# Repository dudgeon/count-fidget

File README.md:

# Count Fidget

A lightweight, rechargeable two-key fidget that counts clicks, resets with a second key, and remembers its count while asleep or unpowered. Designed for a home-printed enclosure and professionally assembled electronics.

**Q5 is the active engineering candidate:** the Q4 STM32L072CBT6 / USB-C home programming / SPI OLED / SPI FRAM design, plus:
- a soft power key (COUNT turns it on; it switches itself off after 30 s, drawing ~8 µA);
- a vendor-soldered LIR2032 coin-cell holder in place of a custom battery pack;
- a battery gauge with LO warning and storage cut-off, and charge status;
- a reset pinhole;
- hold-to-reset key logic;
- a smaller 47.2 × 59.2 × 16.8 mm printed enclosure with printed keycaps;
- solder-free keys (clicky switches pressed into vendor-placed hot-swap sockets).

JLC performs all SMT from standard inventory parts. Two JLCPCB variants are prepared:
- **A:** the user solders the display header (14 joints);
- **B:** JLC also fits the display.

Q1–Q4 remain historical, unchanged packages.

**The design is locked, and a first-article batch of 5 assembled boards was ordered from JLCPCB on 26 September 2026** (see [JLC-QUOTE-Q5](procurement/q5/JLC-QUOTE-Q5.md)). Nothing has been built or measured yet. The boards will be checked against the [first-article test plan](docs/q5-first-article-test-plan.md).

Start with [the Q5 engineering review](docs/REVIEW-Q5-2026-09-25.md), [PROJECT.md](PROJECT.md) for status, and [HANDOFF.md](HANDOFF.md) for continuation.

| Area | Current Q5 files |
|---|---|
| PCB | [KiCad project](electronics/q5/click-counter-Q5.kicad_pro), [board](electronics/q5/click-counter-Q5.kicad_pcb), [schematic PDF](electronics/q5/schematic-Q5.pdf), [power design](docs/q5-power-design.md) |
| Firmware and programming | [Q5 source/build](firmware/q5-stm32/README.md), [keys, power and USB procedure](docs/q5-firmware.md), [macOS flashing tool](tools/clicker-flash/README.md) (Claude skill `flash-clickers`) |
| Inventory, assembly and quote | [Stock evidence](procurement/q5/stock.json), [exports](procurement/q5/REVIEW-EXPORTS-Q5.md), [JLCPCB quote and estimate](procurement/q5/JLC-QUOTE-Q5.md) |
| Enclosure | [Assembly and parts](mechanical/q5/README.md), [rendering](mechanical/q5/assembled-Q5.png), [STEP assembly](mechanical/q5/enclosure-Q5.step) |
| Verification | [Build workflow](docs/build-and-verify.md), Q5 reports in `verification/`, [firmware emulation](simulation/q5-firmware-emulation/README.md), [bounded power checks](simulation/q5-power/result.json) |
| Product history | [Specification](docs/product-spec.md), [user context](docs/user-research.md), [decisions](docs/decisions.md), [Q4 review](docs/REVIEW-Q4-2026-09-24.md), [Q4 simulation review](docs/REVIEW-Q4-simulation-2026-09-25.md) |
| Vendor history | [Vendor status](procurement/vendor-status.md); retained RFQ packages in `dist/` do not authorize new submissions |

Quick checks, with Python 3 and a C compiler:

```sh
python3 scripts/verify_project.py
python3 scripts/run_host_tests.py
```

These verify files, package consistency and portable firmware logic, not physical electronics. Toolchains, credentials, private mailbox content and customer account sessions are not stored in this public repository.

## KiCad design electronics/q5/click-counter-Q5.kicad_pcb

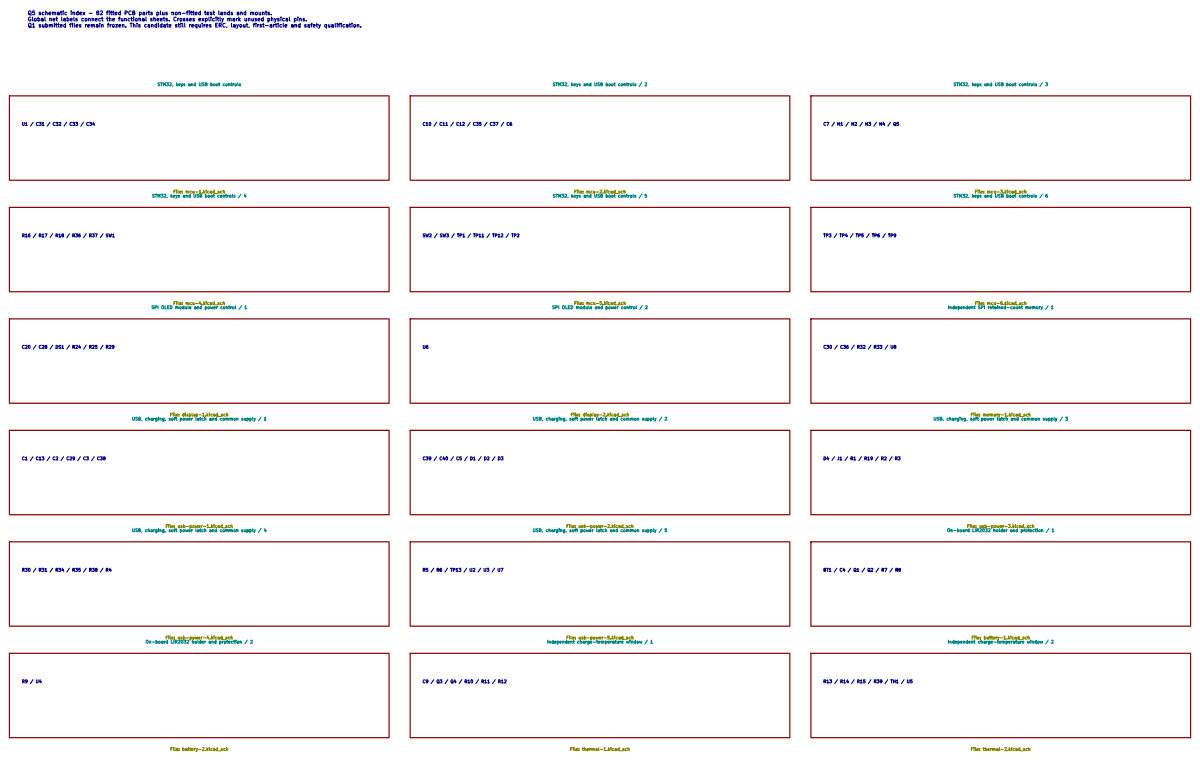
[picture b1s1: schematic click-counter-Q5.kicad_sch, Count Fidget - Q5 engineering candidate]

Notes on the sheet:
Q5 schematic index - 82 fitted PCB parts plus non-fitted test lands and mounts. Global net labels connect the functional sheets. Crosses explicitly mark unused physical pins. Q1 submitted files remain frozen. This candidate still requires ERC, layout, first-article and safety qualification.
U1 / C31 / C32 / C33 / C34
C10 / C11 / C12 / C35 / C37 / C6
C7 / H1 / H2 / H3 / H4 / Q5
R16 / R17 / R18 / R36 / R37 / SW1
SW2 / SW3 / TP1 / TP11 / TP12 / TP2
TP3 / TP4 / TP5 / TP6 / TP9
C20 / C28 / DS1 / R24 / R25 / R29
C30 / C36 / R32 / R33 / U8
C1 / C13 / C2 / C29 / C3 / C38
C39 / C40 / C5 / D1 / D2 / D3
D4 / J1 / R1 / R19 / R2 / R3
R30 / R31 / R34 / R35 / R38 / R4
R5 / R6 / TP13 / U2 / U3 / U7
BT1 / C4 / Q1 / Q2 / R7 / R8
R9 / U4
C9 / Q3 / Q4 / R10 / R11 / R12
R13 / R14 / R15 / R39 / TH1 / U5

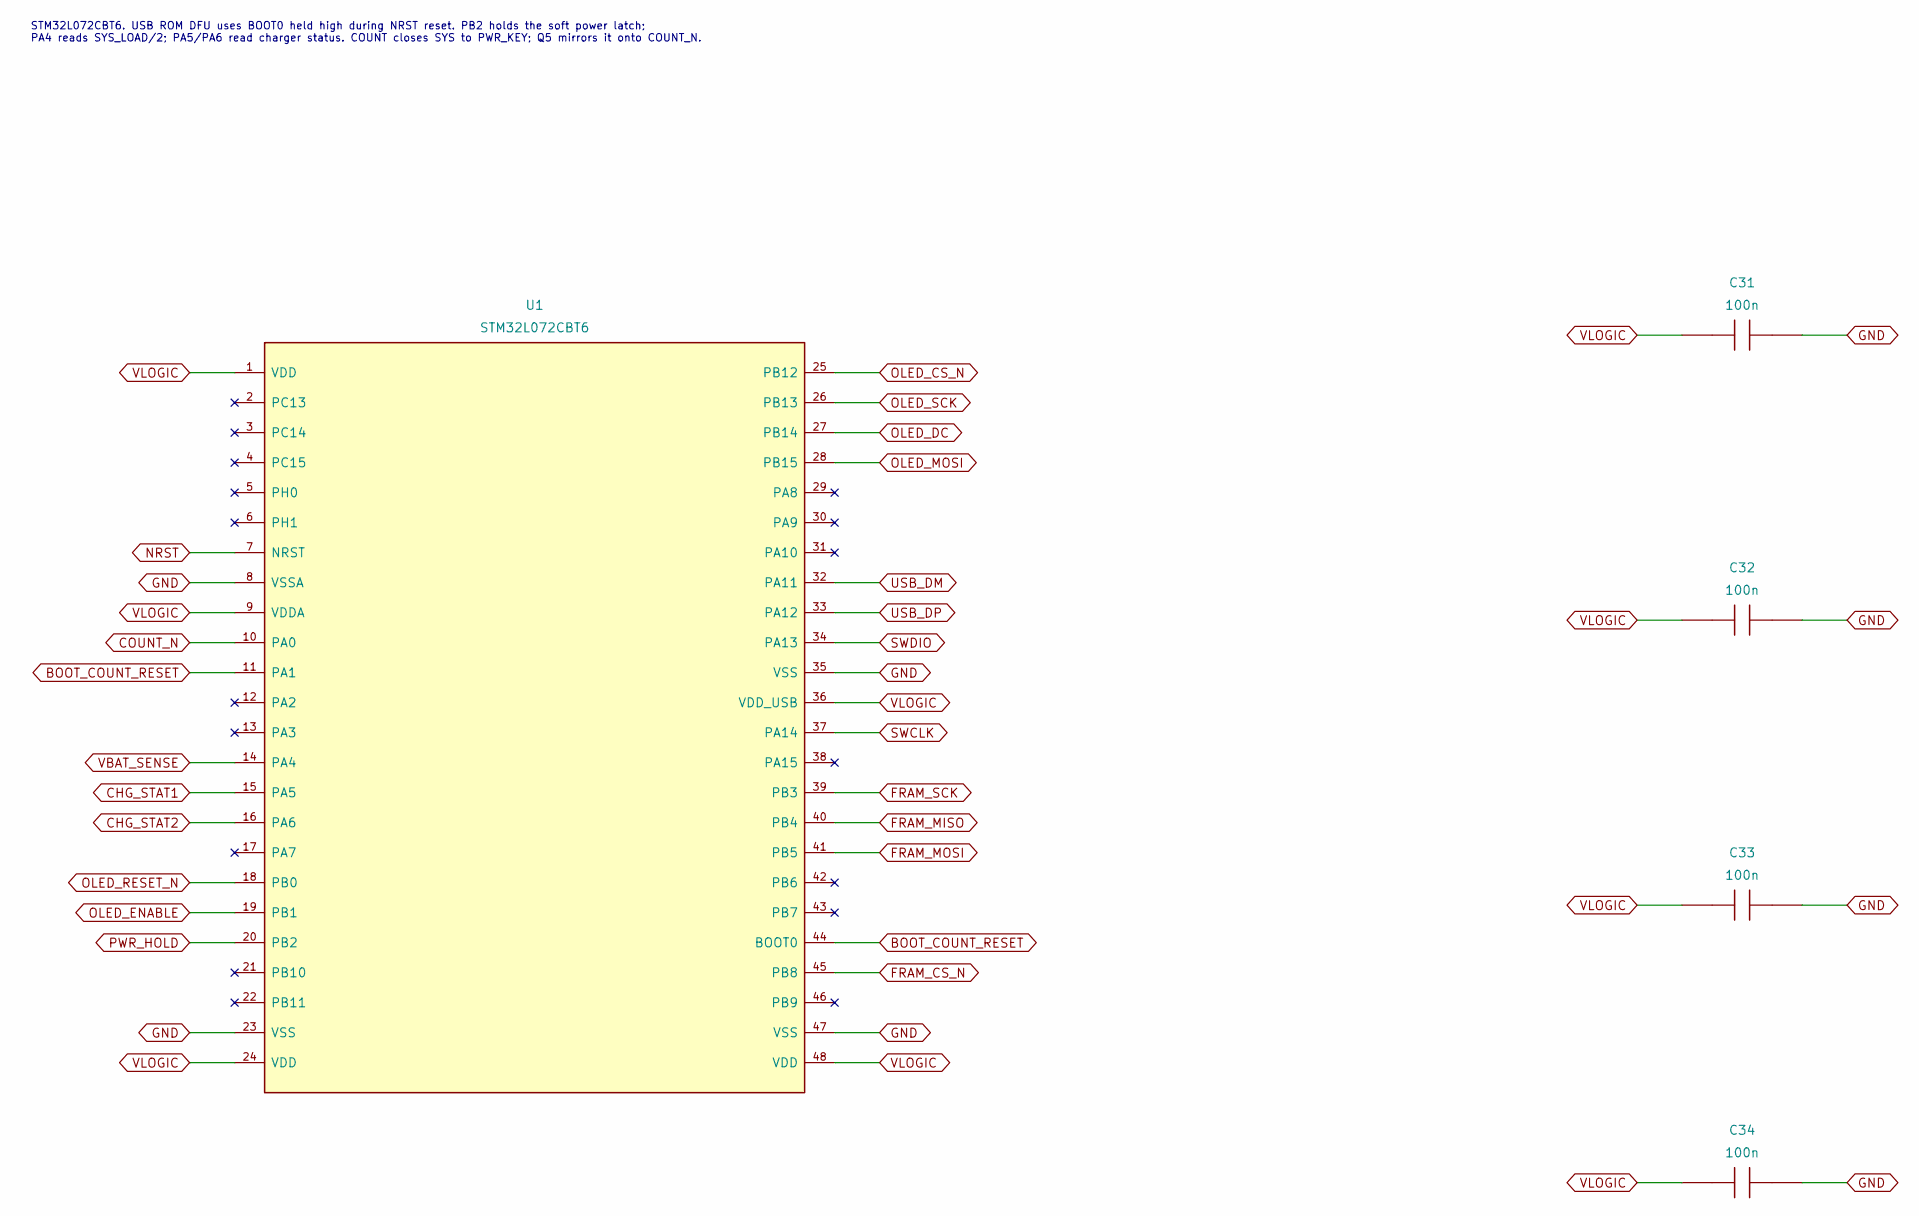
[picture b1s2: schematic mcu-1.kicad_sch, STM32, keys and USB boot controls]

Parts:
C31, C32, C33, C34: 100n; Capacitor_SMD_C_0603_1608Metric; MPN CC0603KRX7R9BB104
U1: STM32L072CBT6; Package_QFP_LQFP-48_7x7mm_P0.5mm; MPN STM32L072CBT6

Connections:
BOOT_COUNT_RESET: U1.11 (PA1), U1.44 (BOOT0); also elsewhere on the board
CHG_STAT1: U1.15 (PA5); also elsewhere on the board
CHG_STAT2: U1.16 (PA6); also elsewhere on the board
COUNT_N: U1.10 (PA0); also elsewhere on the board
FRAM_CS_N: U1.45 (PB8); also elsewhere on the board
FRAM_MISO: U1.40 (PB4); also elsewhere on the board
FRAM_MOSI: U1.41 (PB5); also elsewhere on the board
FRAM_SCK: U1.39 (PB3); also elsewhere on the board
GND: C31.2, C32.2, C33.2, C34.2, U1.8 (VSSA), U1.23 (VSS), U1.35 (VSS), U1.47 (VSS); also elsewhere on the board
NRST: U1.7 (NRST); also elsewhere on the board
OLED_CS_N: U1.25 (PB12); also elsewhere on the board
OLED_DC: U1.27 (PB14); also elsewhere on the board
OLED_ENABLE: U1.19 (PB1); also elsewhere on the board
OLED_MOSI: U1.28 (PB15); also elsewhere on the board
OLED_RESET_N: U1.18 (PB0); also elsewhere on the board
OLED_SCK: U1.26 (PB13); also elsewhere on the board
PWR_HOLD: U1.20 (PB2); also elsewhere on the board
SWCLK: U1.37 (PA14); also elsewhere on the board
SWDIO: U1.34 (PA13); also elsewhere on the board
USB_DM: U1.32 (PA11); also elsewhere on the board
USB_DP: U1.33 (PA12); also elsewhere on the board
VBAT_SENSE: U1.14 (PA4); also elsewhere on the board
VLOGIC: C31.1, C32.1, C33.1, C34.1, U1.1 (VDD), U1.9 (VDDA), U1.24 (VDD), U1.36 (VDD_USB), U1.48 (VDD); also elsewhere on the board

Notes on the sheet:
STM32L072CBT6. USB ROM DFU uses BOOT0 held high during NRST reset. PB2 holds the soft power latch; PA4 reads SYS_LOAD/2; PA5/PA6 read charger status. COUNT closes SYS to PWR_KEY; Q5 mirrors it onto COUNT_N.

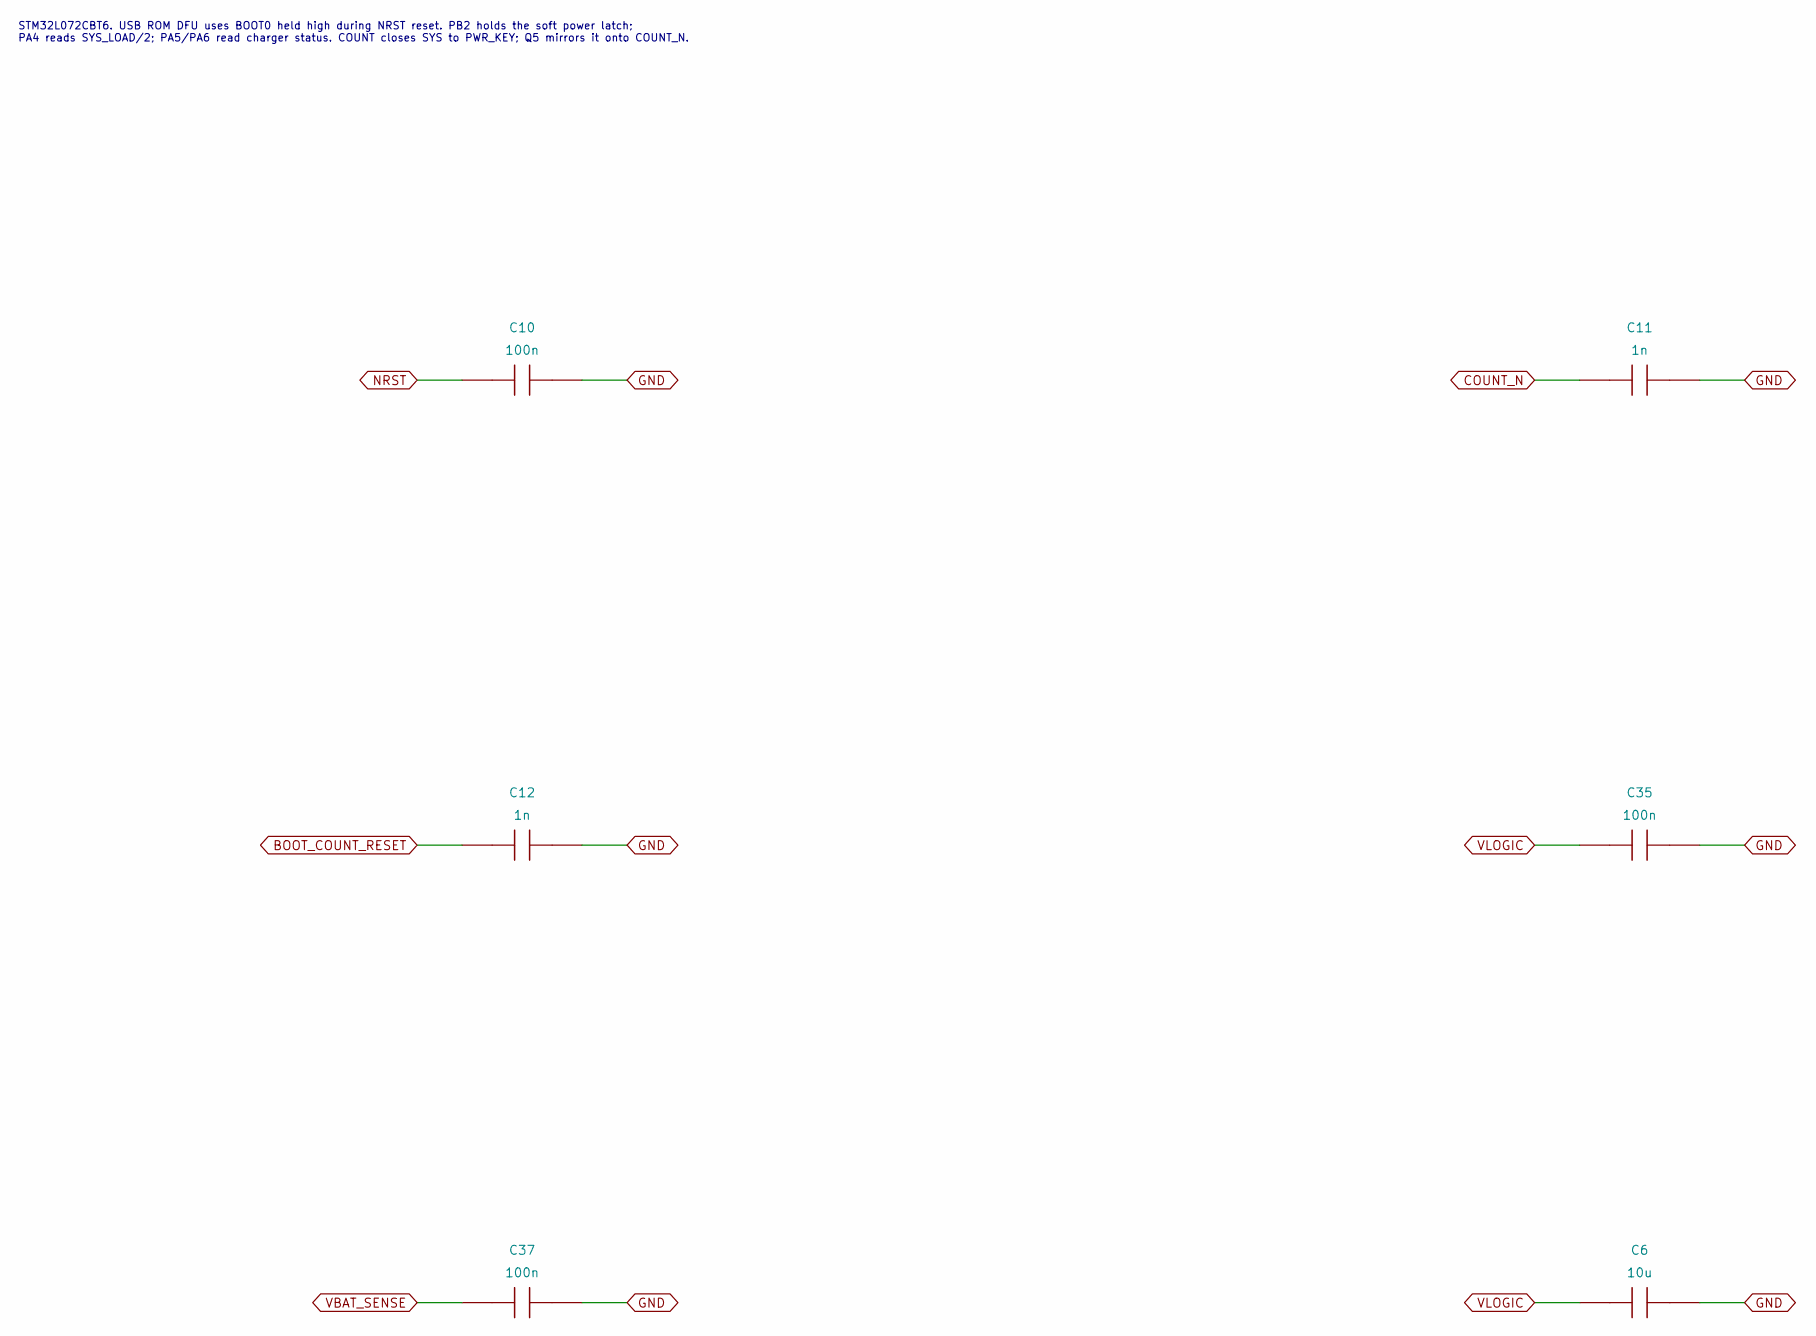
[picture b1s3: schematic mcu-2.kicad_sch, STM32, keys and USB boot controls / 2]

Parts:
C6: 10u; Capacitor_SMD_C_0805_2012Metric; MPN GRM21BR61H106KE43L
C10, C35, C37: 100n; Capacitor_SMD_C_0603_1608Metric; MPN CC0603KRX7R9BB104
C11, C12: 1n; Capacitor_SMD_C_0603_1608Metric; MPN CL10B102KB8NNNC

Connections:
BOOT_COUNT_RESET: C12.1; also elsewhere on the board
COUNT_N: C11.1; also elsewhere on the board
GND: C6.2, C10.2, C11.2, C12.2, C35.2, C37.2; also elsewhere on the board
NRST: C10.1; also elsewhere on the board
VBAT_SENSE: C37.1; also elsewhere on the board
VLOGIC: C6.1, C35.1; also elsewhere on the board

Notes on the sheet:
STM32L072CBT6. USB ROM DFU uses BOOT0 held high during NRST reset. PB2 holds the soft power latch; PA4 reads SYS_LOAD/2; PA5/PA6 read charger status. COUNT closes SYS to PWR_KEY; Q5 mirrors it onto COUNT_N.

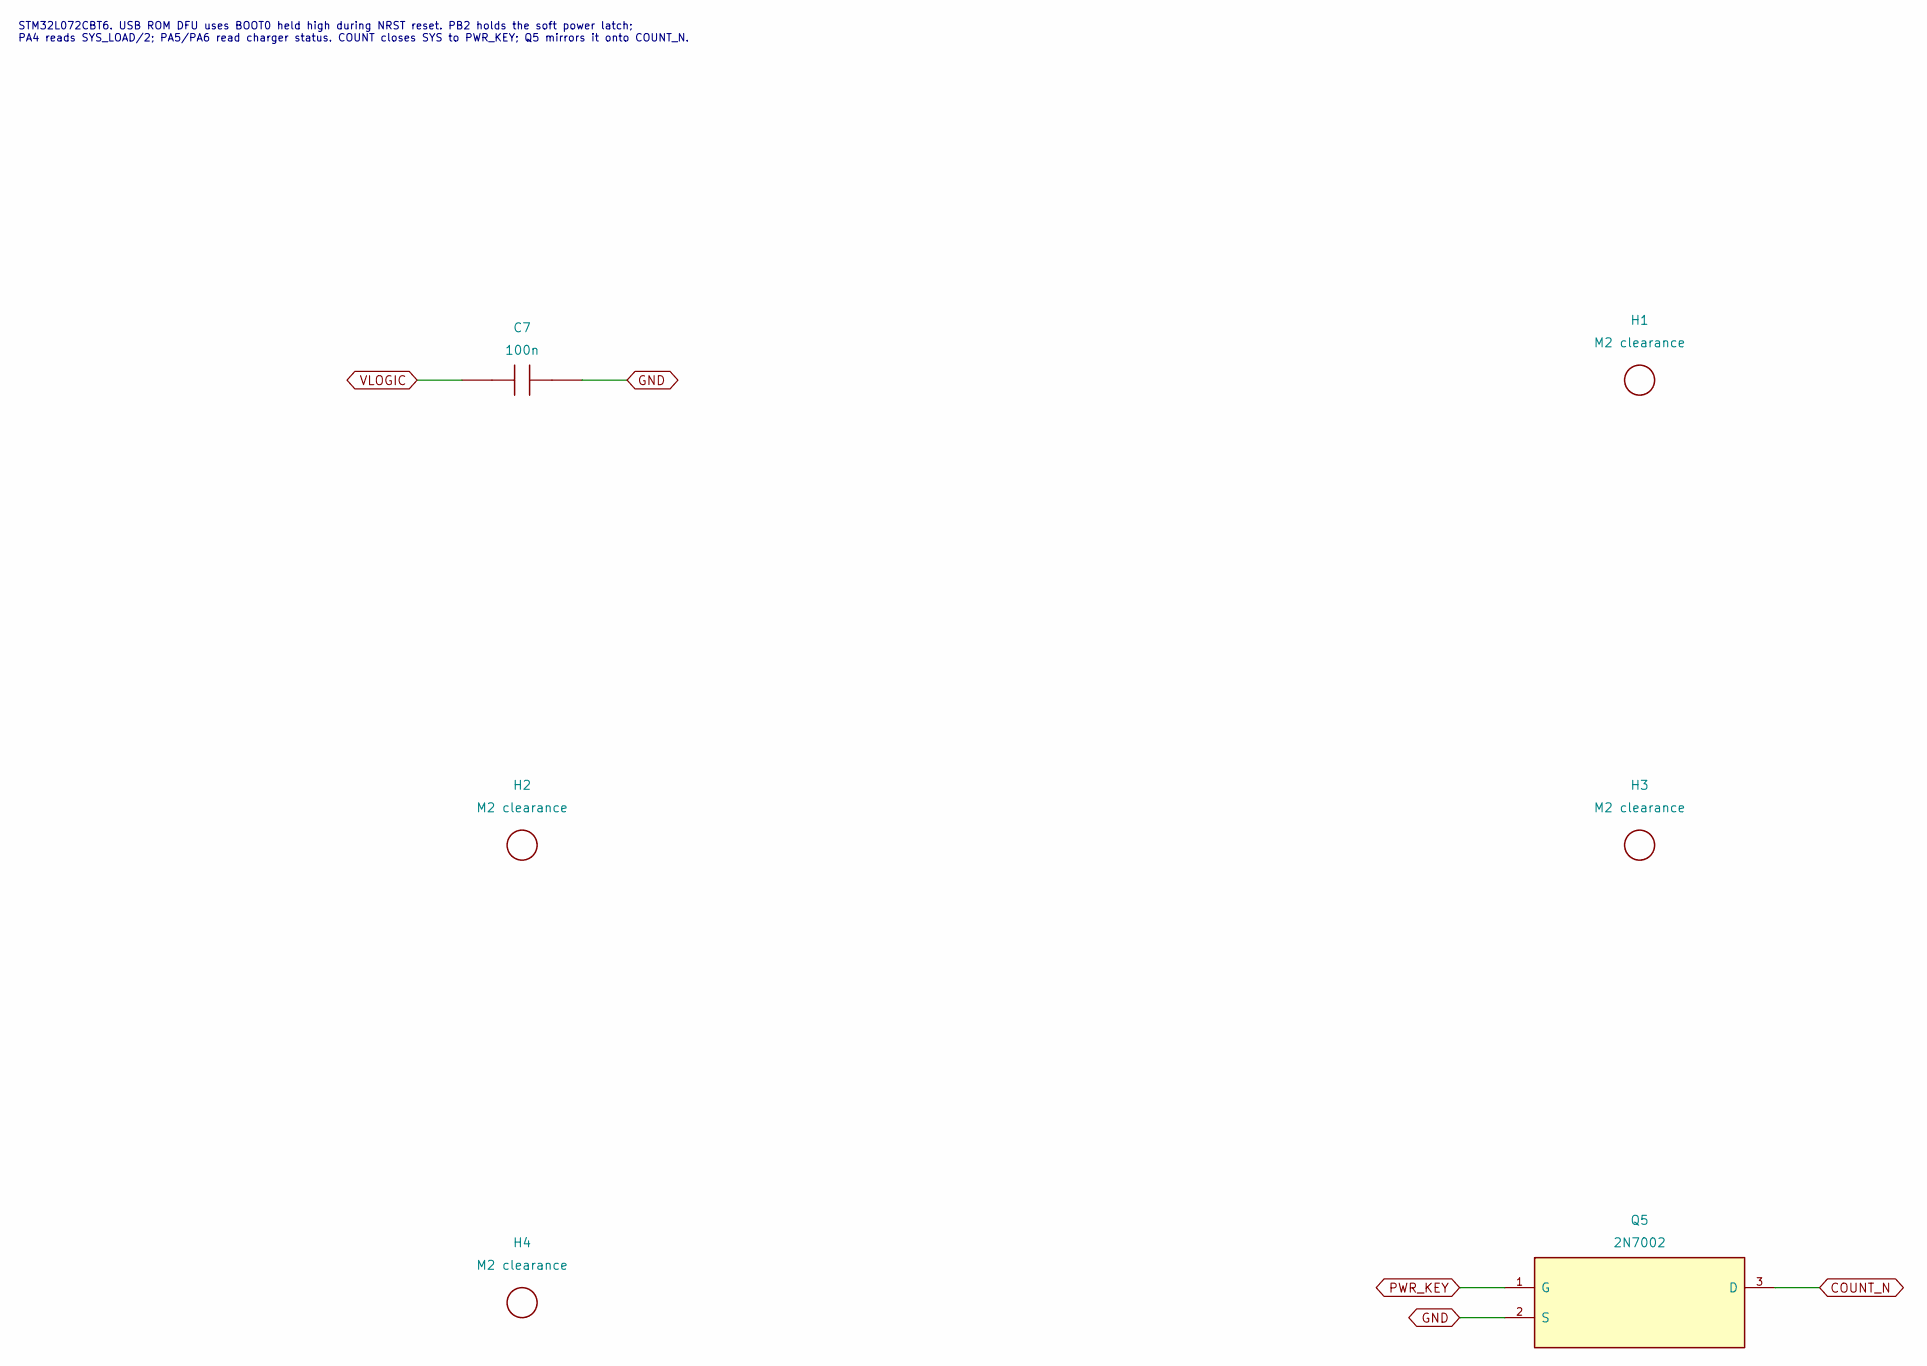
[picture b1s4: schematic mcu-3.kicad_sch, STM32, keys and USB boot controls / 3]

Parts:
C7: 100n; Capacitor_SMD_C_0603_1608Metric; MPN CC0603KRX7R9BB104
H1, H2, H3, H4: M2 clearance; MountingHole_MountingHole_2.2mm_M2; MPN NPTH
Q5: COUNT key level shift; Package_TO_SOT_SMD_SOT-23; MPN 2N7002

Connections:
COUNT_N: Q5.3 (D); also elsewhere on the board
GND: C7.2, Q5.2 (S); also elsewhere on the board
PWR_KEY: Q5.1 (G); also elsewhere on the board
VLOGIC: C7.1; also elsewhere on the board

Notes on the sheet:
STM32L072CBT6. USB ROM DFU uses BOOT0 held high during NRST reset. PB2 holds the soft power latch; PA4 reads SYS_LOAD/2; PA5/PA6 read charger status. COUNT closes SYS to PWR_KEY; Q5 mirrors it onto COUNT_N.

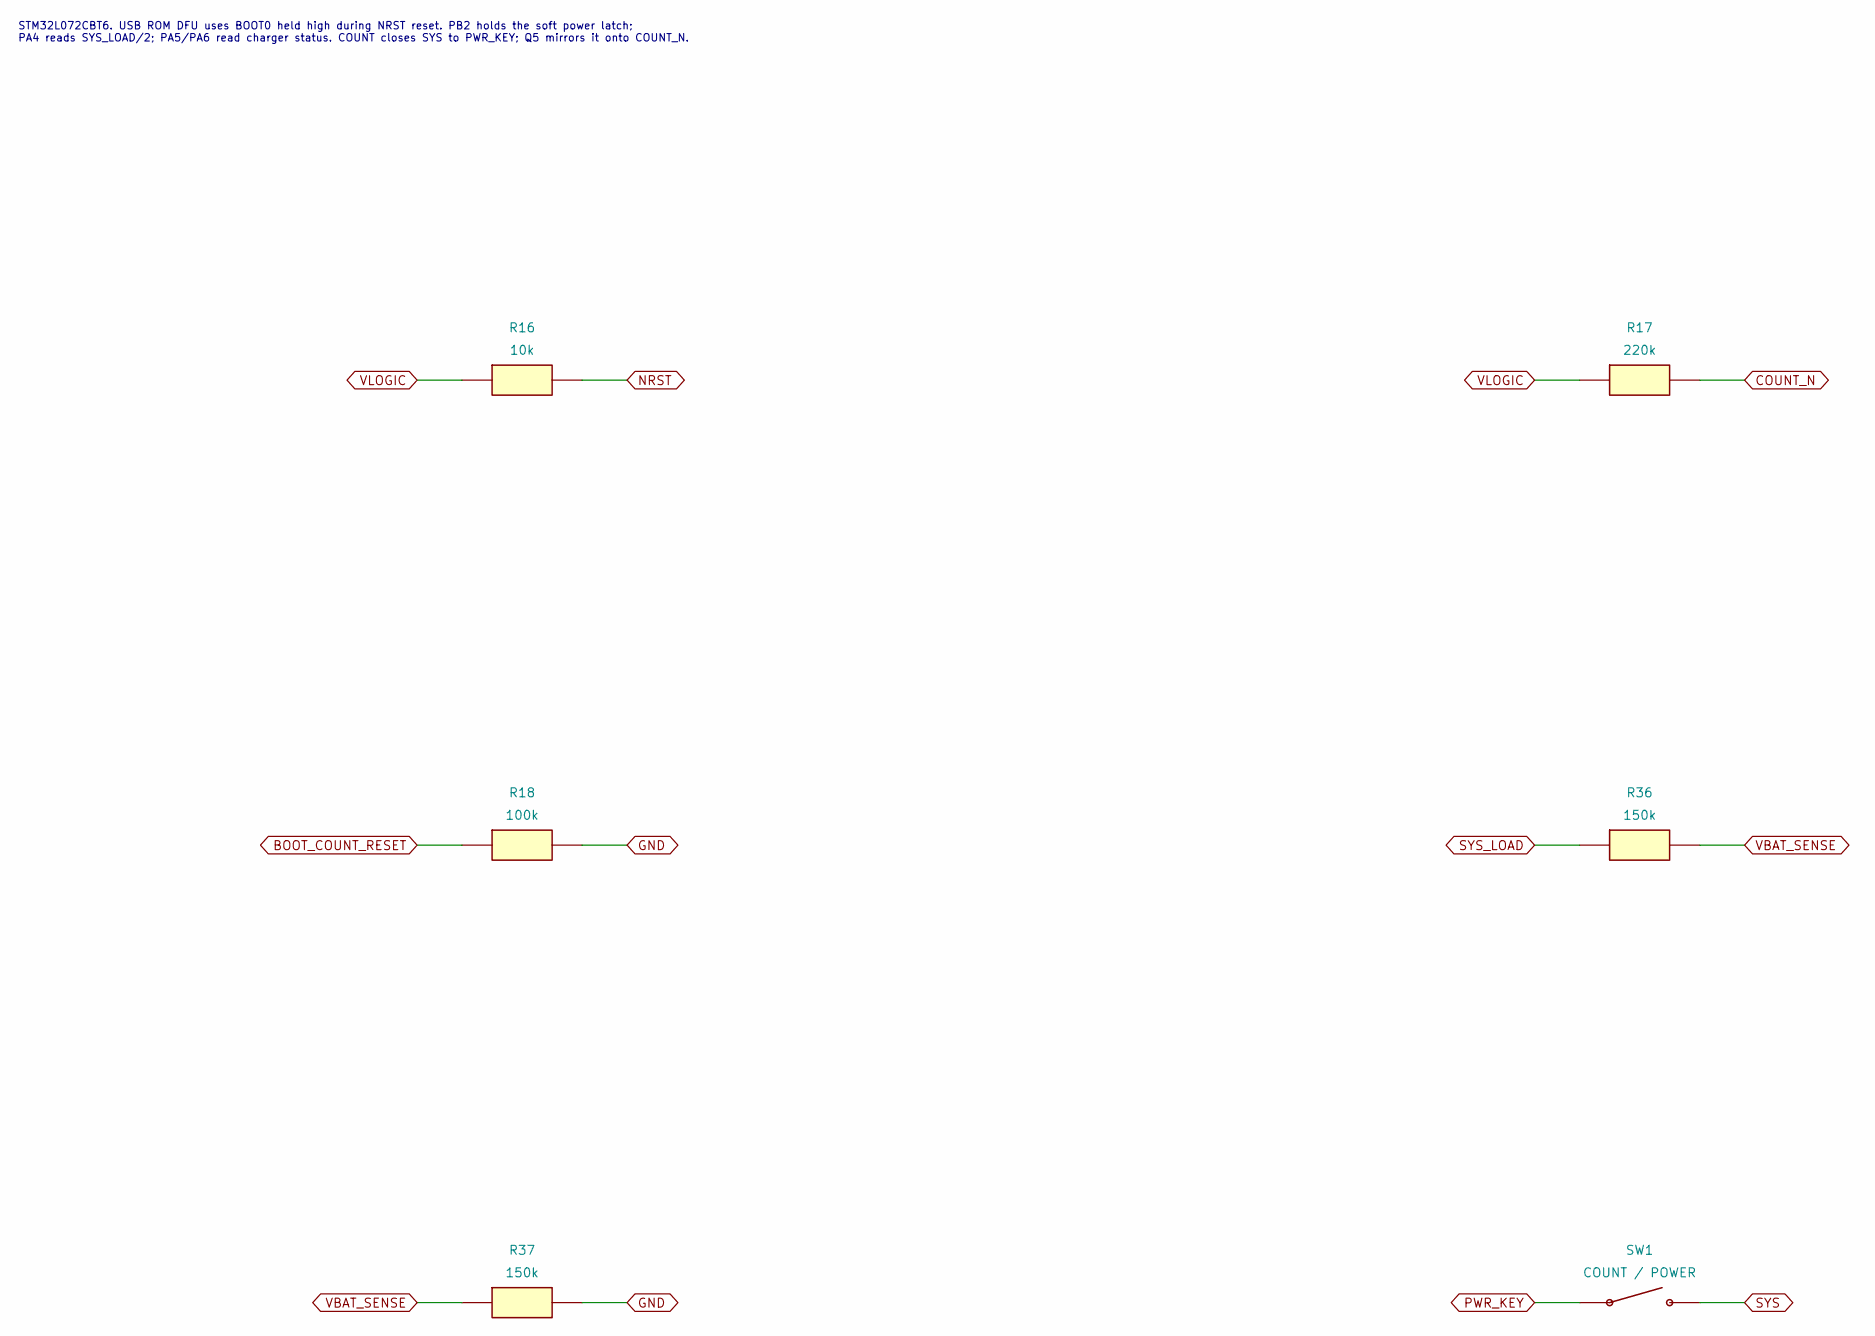
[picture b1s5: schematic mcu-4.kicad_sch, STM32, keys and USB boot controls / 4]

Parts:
R16: 10k; Resistor_SMD_R_0603_1608Metric; MPN 0603WAF1002T5E
R17: 220k; Resistor_SMD_R_0603_1608Metric; MPN 0603WAF2203T5E
R18: 100k; Resistor_SMD_R_0603_1608Metric; MPN 0603WAF1003T5E
R36, R37: 150k; Resistor_SMD_R_0603_1608Metric; MPN RT0603BRD07150KL
SW1: COUNT / POWER; SW_Hotswap_Kailh_MX_CPG151101S11; MPN CPG151101S11-16

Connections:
BOOT_COUNT_RESET: R18.1; also elsewhere on the board
COUNT_N: R17.2; also elsewhere on the board
GND: R18.2, R37.2; also elsewhere on the board
NRST: R16.2; also elsewhere on the board
PWR_KEY: SW1.1; also elsewhere on the board
SYS: SW1.2; also elsewhere on the board
SYS_LOAD: R36.1; also elsewhere on the board
VBAT_SENSE: R36.2, R37.1; also elsewhere on the board
VLOGIC: R16.1, R17.1; also elsewhere on the board

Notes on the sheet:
STM32L072CBT6. USB ROM DFU uses BOOT0 held high during NRST reset. PB2 holds the soft power latch; PA4 reads SYS_LOAD/2; PA5/PA6 read charger status. COUNT closes SYS to PWR_KEY; Q5 mirrors it onto COUNT_N.

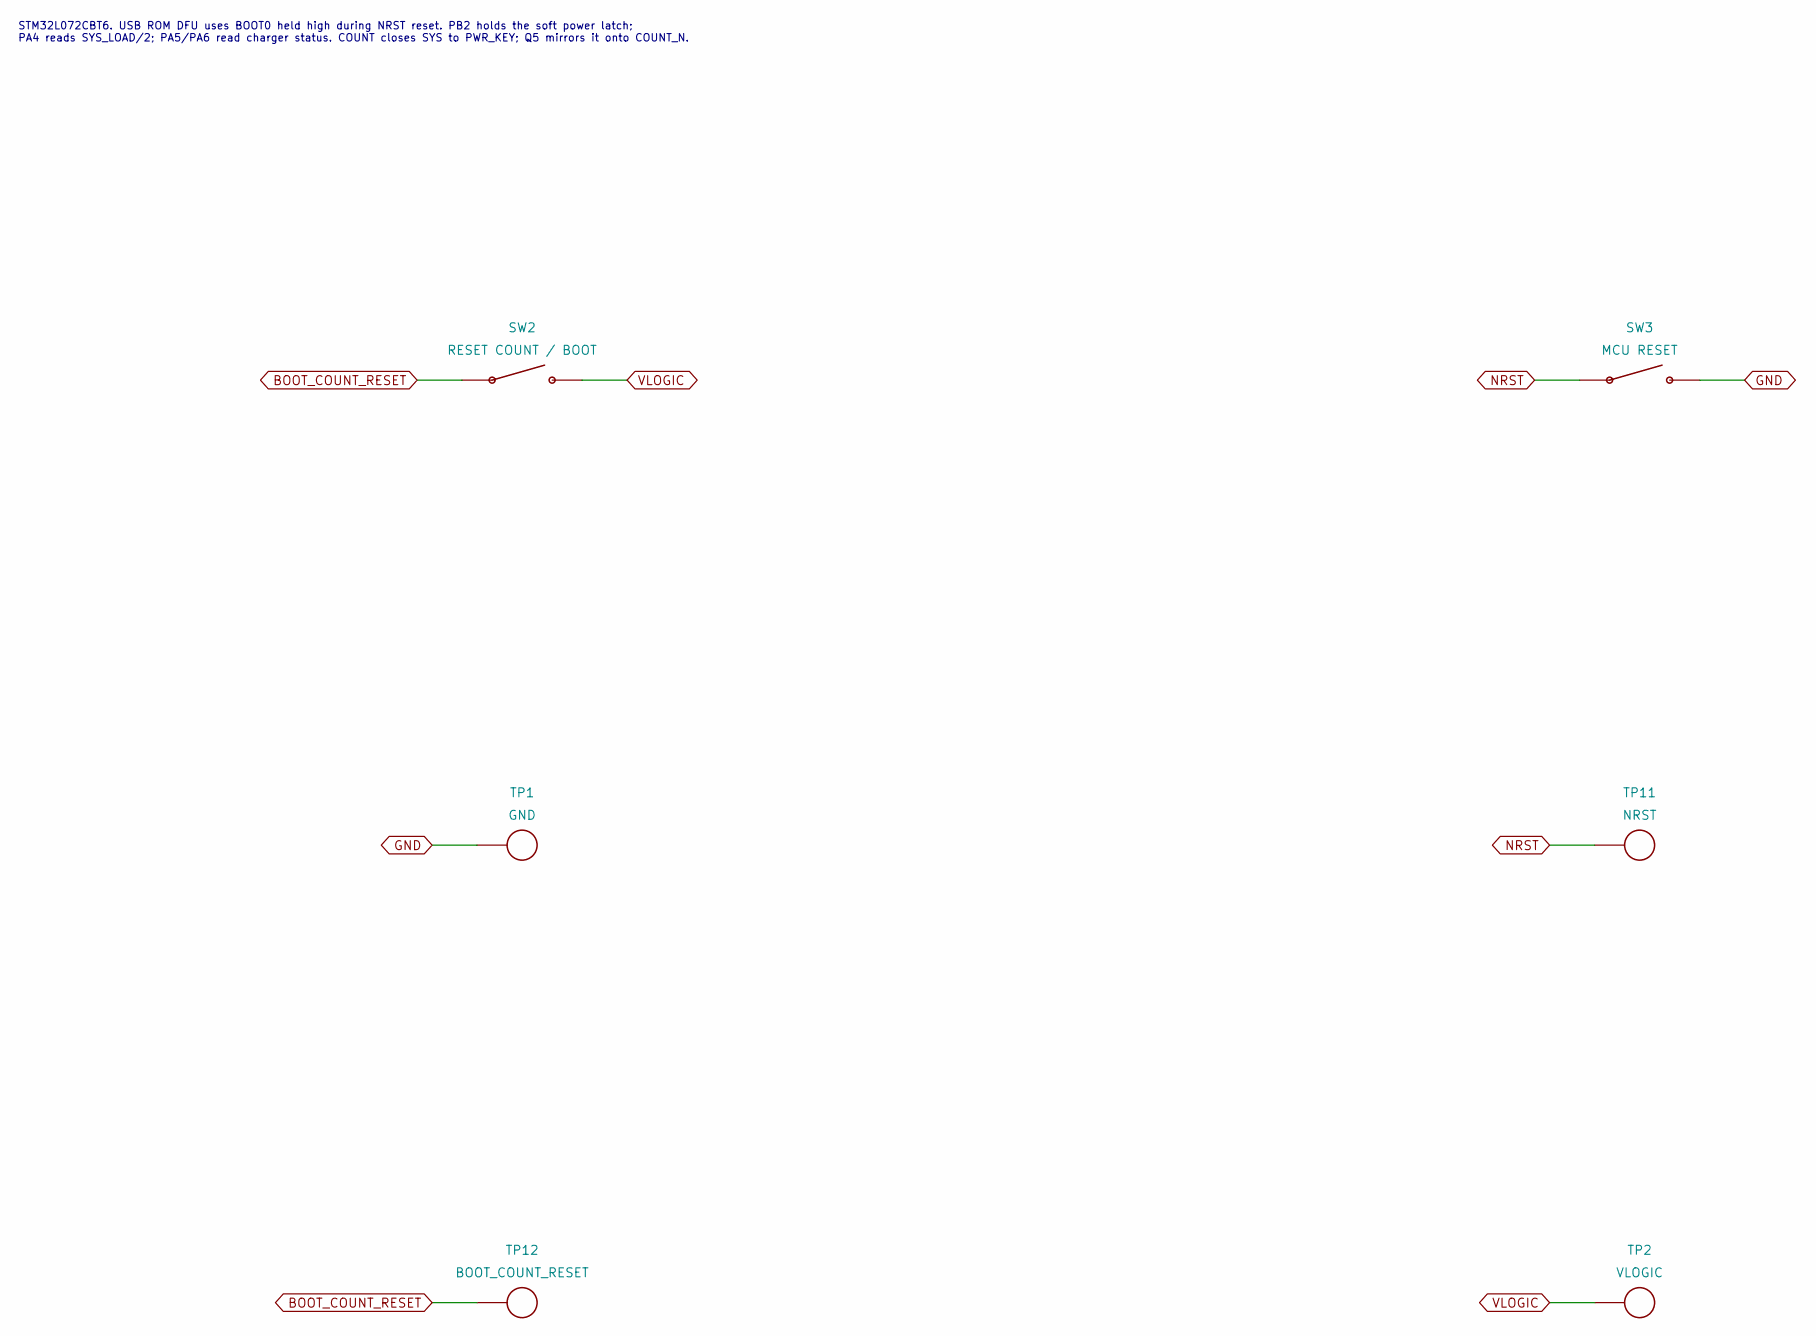
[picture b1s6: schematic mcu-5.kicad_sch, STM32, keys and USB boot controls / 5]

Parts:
SW2: RESET COUNT / BOOT; SW_Hotswap_Kailh_MX_CPG151101S11; MPN CPG151101S11-16
SW3: MCU RESET; XUNPU_TS-1088-AR02016_SMD; MPN TS-1088-AR02016
TP1: GND; TestPoint_TestPoint_Pad_D1.5mm; MPN PCB LAND
TP2: VLOGIC; TestPoint_TestPoint_Pad_D1.5mm; MPN PCB LAND
TP11: NRST; TestPoint_TestPoint_Pad_D1.5mm; MPN PCB LAND
TP12: BOOT_COUNT_RESET; TestPoint_TestPoint_Pad_D1.5mm; MPN PCB LAND

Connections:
BOOT_COUNT_RESET: SW2.1, TP12.1 (1_1); also elsewhere on the board
GND: SW3.2, TP1.1 (1_1); also elsewhere on the board
NRST: SW3.1, TP11.1 (1_1); also elsewhere on the board
VLOGIC: SW2.2, TP2.1 (1_1); also elsewhere on the board

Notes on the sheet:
STM32L072CBT6. USB ROM DFU uses BOOT0 held high during NRST reset. PB2 holds the soft power latch; PA4 reads SYS_LOAD/2; PA5/PA6 read charger status. COUNT closes SYS to PWR_KEY; Q5 mirrors it onto COUNT_N.

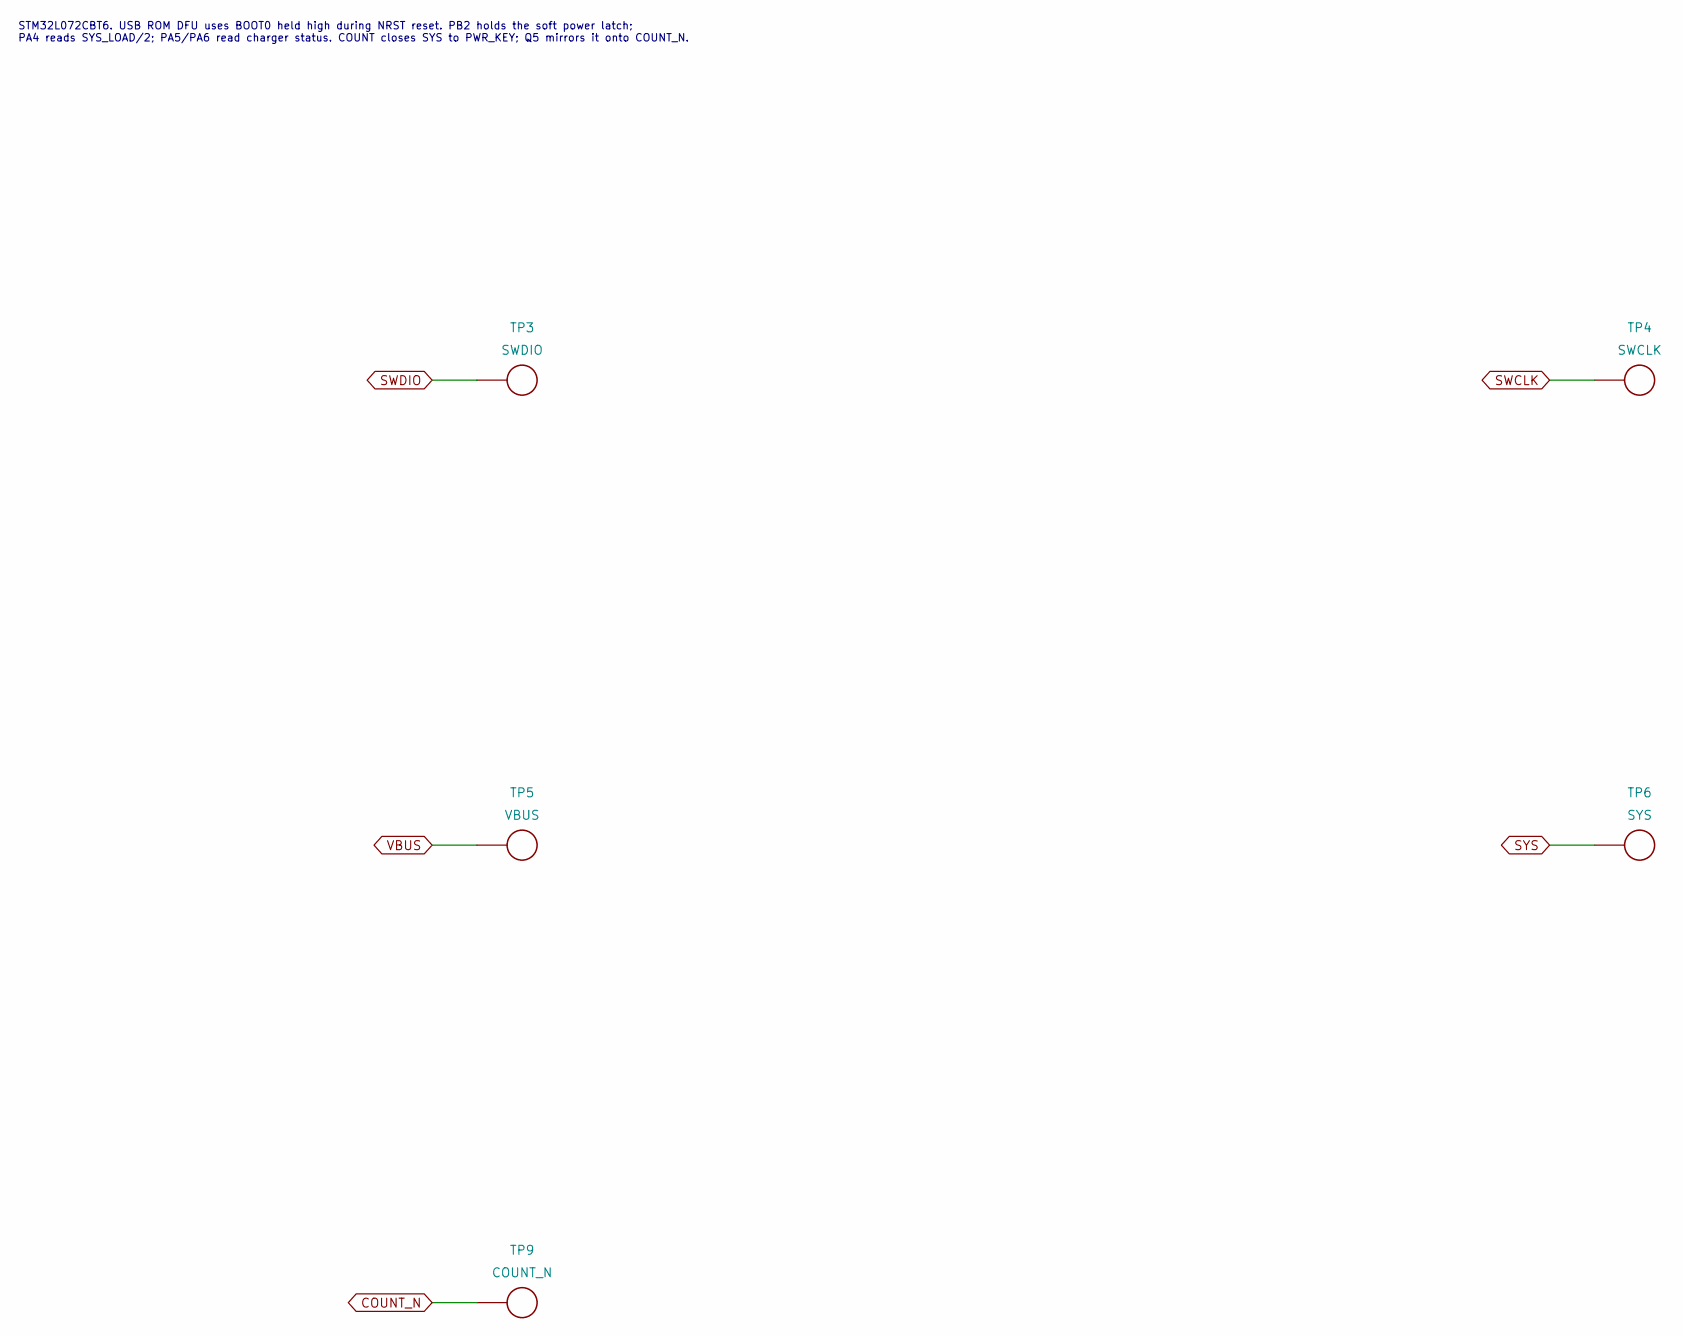
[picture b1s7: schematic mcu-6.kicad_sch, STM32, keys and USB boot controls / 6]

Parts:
TP3: SWDIO; TestPoint_TestPoint_Pad_D1.5mm; MPN PCB LAND
TP4: SWCLK; TestPoint_TestPoint_Pad_D1.5mm; MPN PCB LAND
TP5: VBUS; TestPoint_TestPoint_Pad_D1.5mm; MPN PCB LAND
TP6: SYS; TestPoint_TestPoint_Pad_D1.5mm; MPN PCB LAND
TP9: COUNT_N; TestPoint_TestPoint_Pad_D1.5mm; MPN PCB LAND

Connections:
COUNT_N: TP9.1 (1_1); also elsewhere on the board
SWCLK: TP4.1 (1_1); also elsewhere on the board
SWDIO: TP3.1 (1_1); also elsewhere on the board
SYS: TP6.1 (1_1); also elsewhere on the board
VBUS: TP5.1 (1_1); also elsewhere on the board

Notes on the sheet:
STM32L072CBT6. USB ROM DFU uses BOOT0 held high during NRST reset. PB2 holds the soft power latch; PA4 reads SYS_LOAD/2; PA5/PA6 read charger status. COUNT closes SYS to PWR_KEY; Q5 mirrors it onto COUNT_N.
